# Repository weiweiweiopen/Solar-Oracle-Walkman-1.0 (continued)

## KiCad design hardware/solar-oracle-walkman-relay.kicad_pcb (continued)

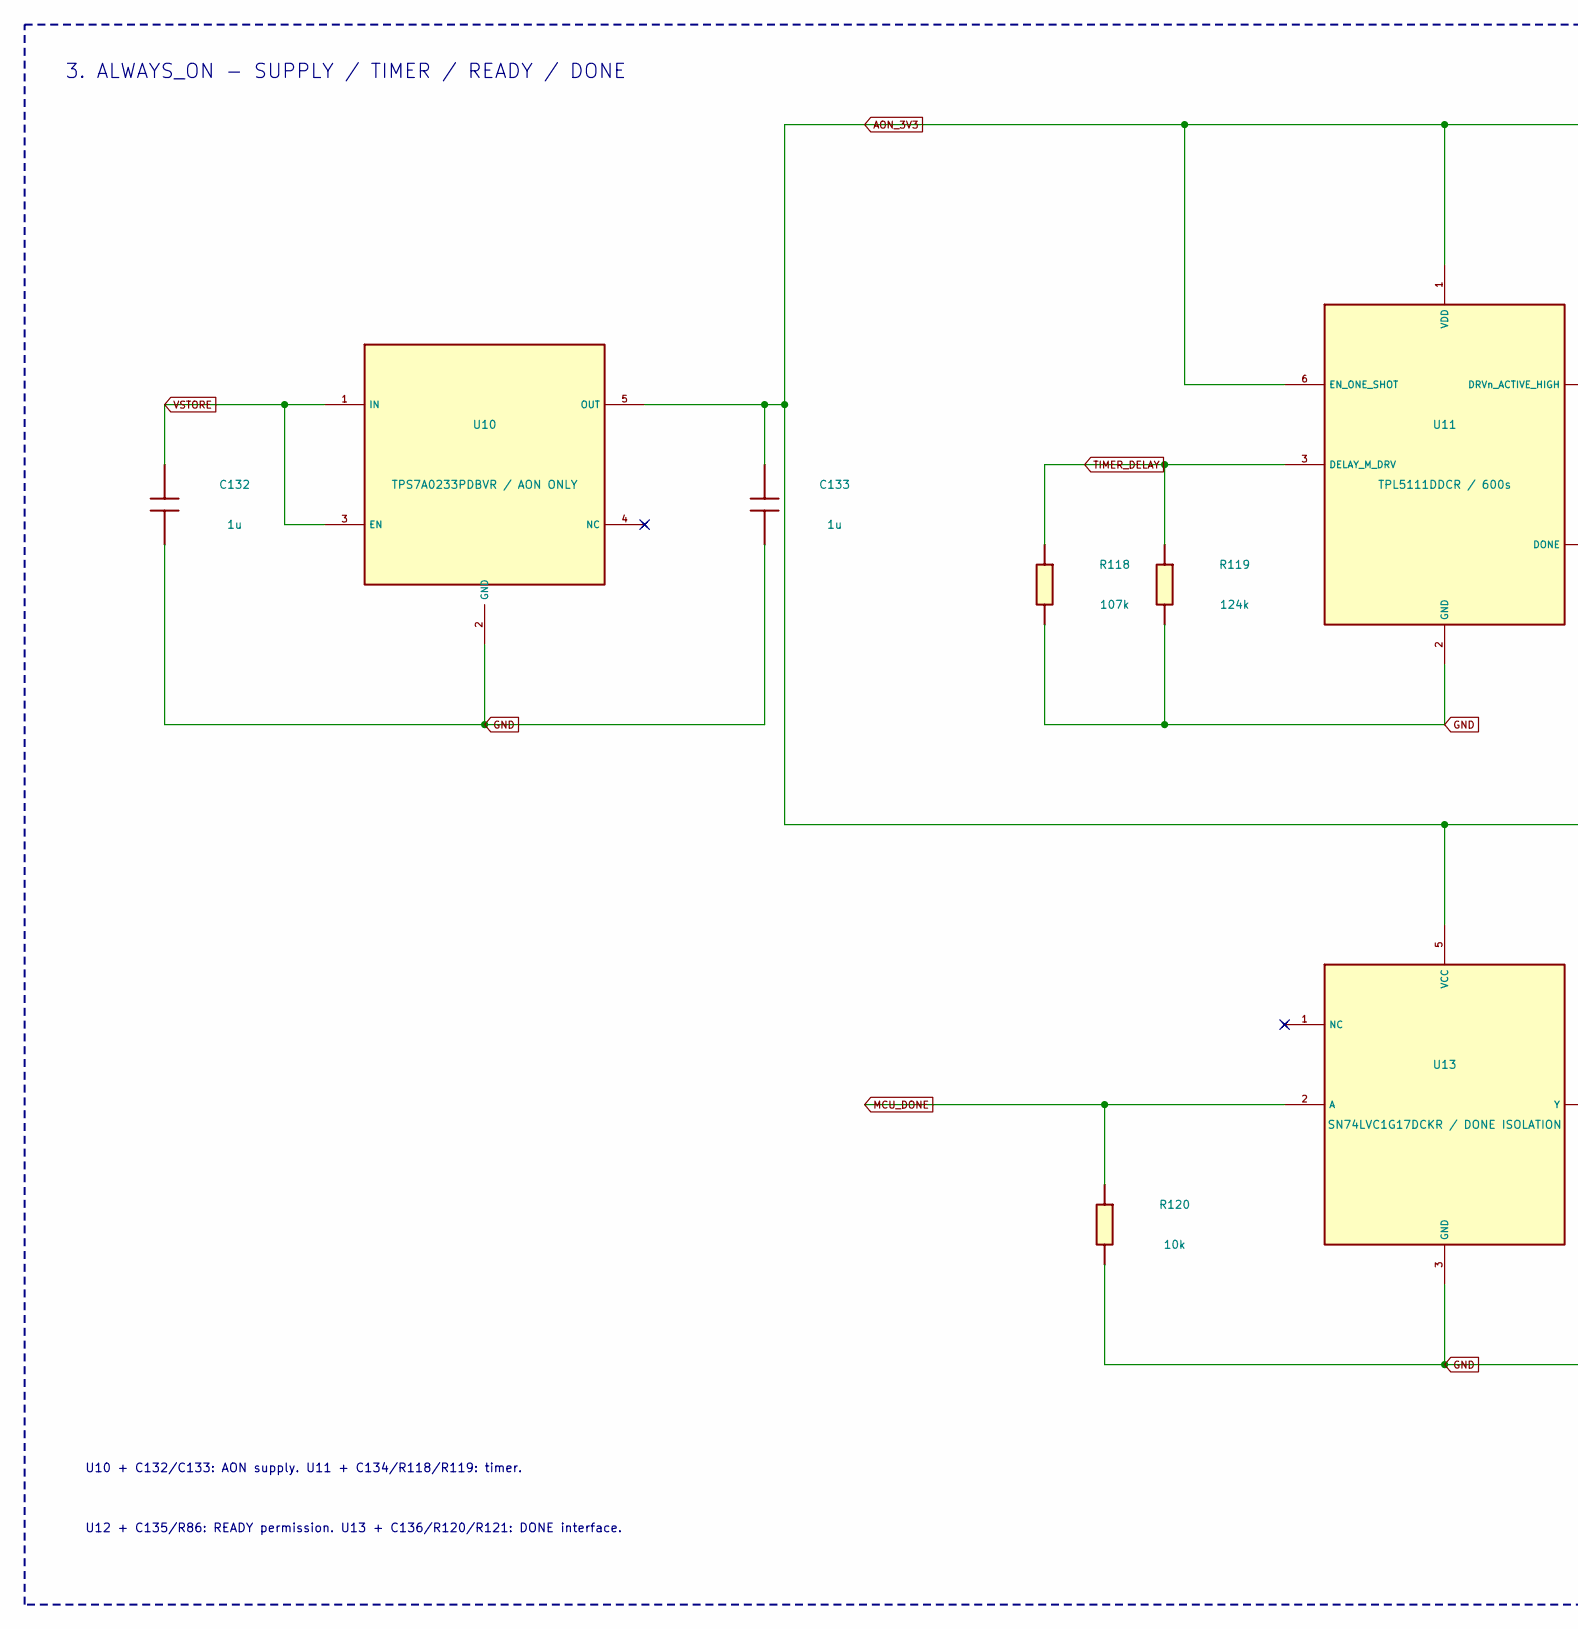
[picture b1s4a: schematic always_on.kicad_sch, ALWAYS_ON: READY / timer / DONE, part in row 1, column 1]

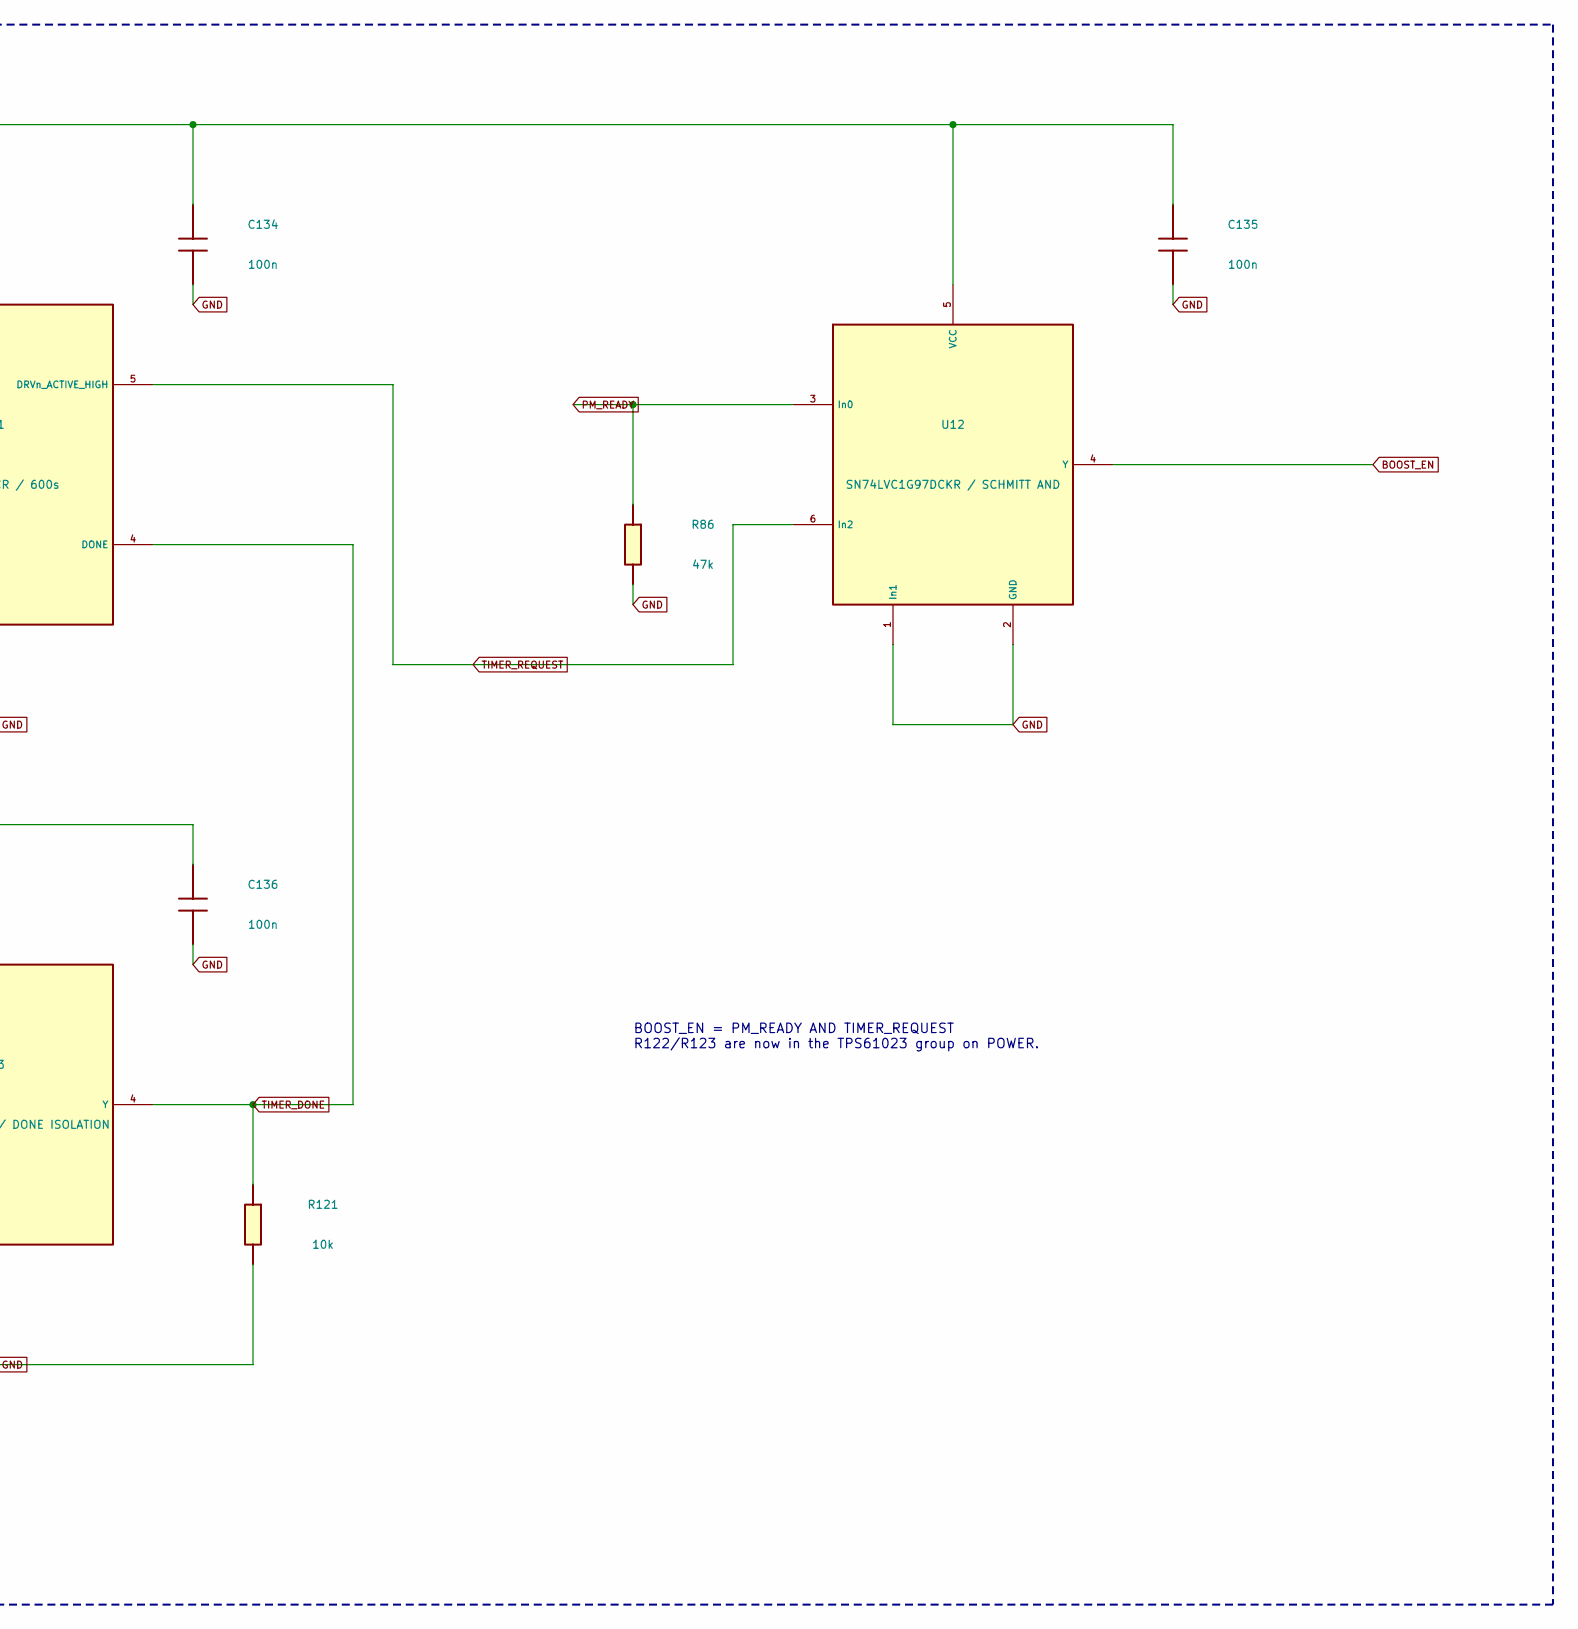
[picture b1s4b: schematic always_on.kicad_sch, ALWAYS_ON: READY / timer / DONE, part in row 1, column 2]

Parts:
C132, C133: 1u; C_0805_2012Metric; MPN GRM21BR71C105KA01L
C134, C135, C136: 100n; C_0805_2012Metric; MPN GRM21BR71H104KA01L
R86: 47k; R_0603_1608Metric; MPN RC0603FR-0747KL
R118: 107k; R_0603_1608Metric; MPN RC0603FR-07107KL
R119: 124k; R_0603_1608Metric; MPN RC0603FR-07124KL
R120, R121: 10k; R_0603_1608Metric; MPN RC0603FR-0710KL
U10: TPS7A0233PDBVR / AON ONLY; SOT-23-5; MPN TPS7A0233PDBVR
U11: TPL5111DDCR / 600s; SOT-23-6; MPN TPL5111DDCR
U12: SN74LVC1G97DCKR / SCHMITT AND; SOT-363_SC-70-6; MPN SN74LVC1G97DCKR
U13: SN74LVC1G17DCKR / DONE ISOLATION; SOT-353_SC-70-5; MPN SN74LVC1G17DCKR

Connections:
AON_3V3: C133.1, C134.1, C135.1, C136.1, U10.5 (OUT), U11.1 (VDD), U11.6 (EN_ONE_SHOT), U12.5 (VCC), U13.5 (VCC)
BOOST_EN: U12.4 (Y); also elsewhere on the board
GND: C132.2, C133.2, C134.2, C135.2, C136.2, R86.2, R118.2, R119.2, R120.2, R121.2, U10.2 (GND), U11.2 (GND), U12.1 (In1), U12.2 (GND), U13.3 (GND); also elsewhere on the board
MCU_DONE: R120.1, U13.2 (A); also elsewhere on the board
PM_READY: R86.1, U12.3 (In0); also elsewhere on the board
TIMER_DELAY: R118.1, R119.1, U11.3 (DELAY_M_DRV)
TIMER_DONE: R121.1, U11.4 (DONE), U13.4 (Y)
TIMER_REQUEST: U11.5 (DRVn_ACTIVE_HIGH), U12.6 (In2)
VSTORE: C132.1, U10.1 (IN), U10.3 (EN); also elsewhere on the board

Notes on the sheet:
U12 + C135/R86: READY permission. U13 + C136/R120/R121: DONE interface.
U10 + C132/C133: AON supply. U11 + C134/R118/R119: timer.
3. ALWAYS_ON - SUPPLY / TIMER / READY / DONE
BOOST_EN = PM_READY AND TIMER_REQUEST R122/R123 are now in the TPS61023 group on POWER.

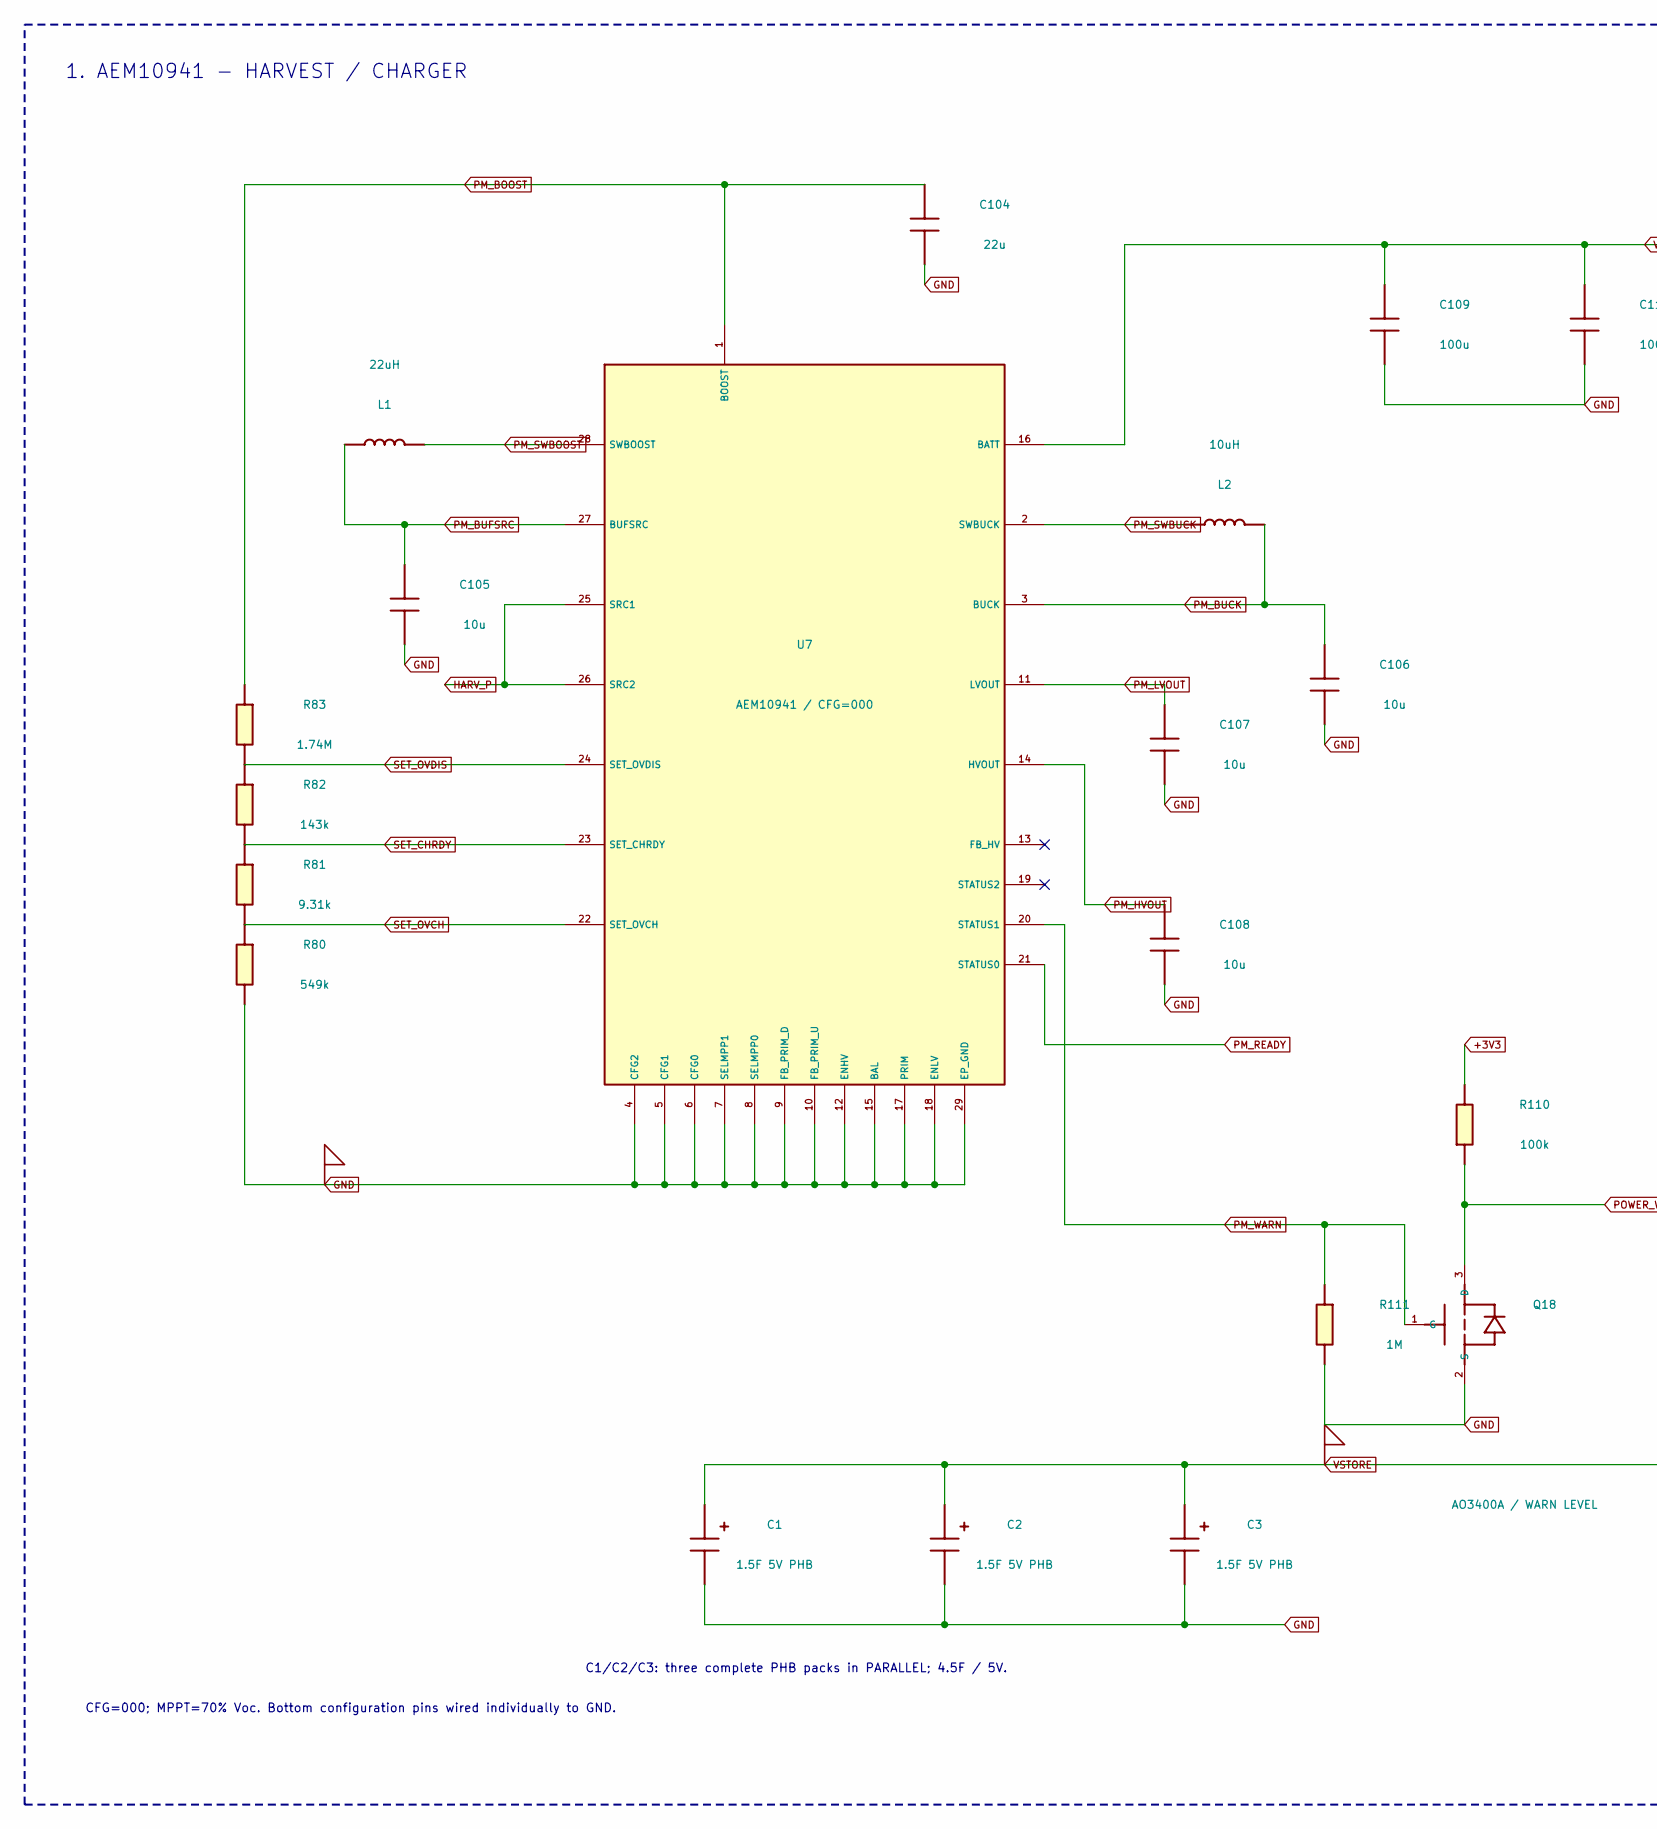
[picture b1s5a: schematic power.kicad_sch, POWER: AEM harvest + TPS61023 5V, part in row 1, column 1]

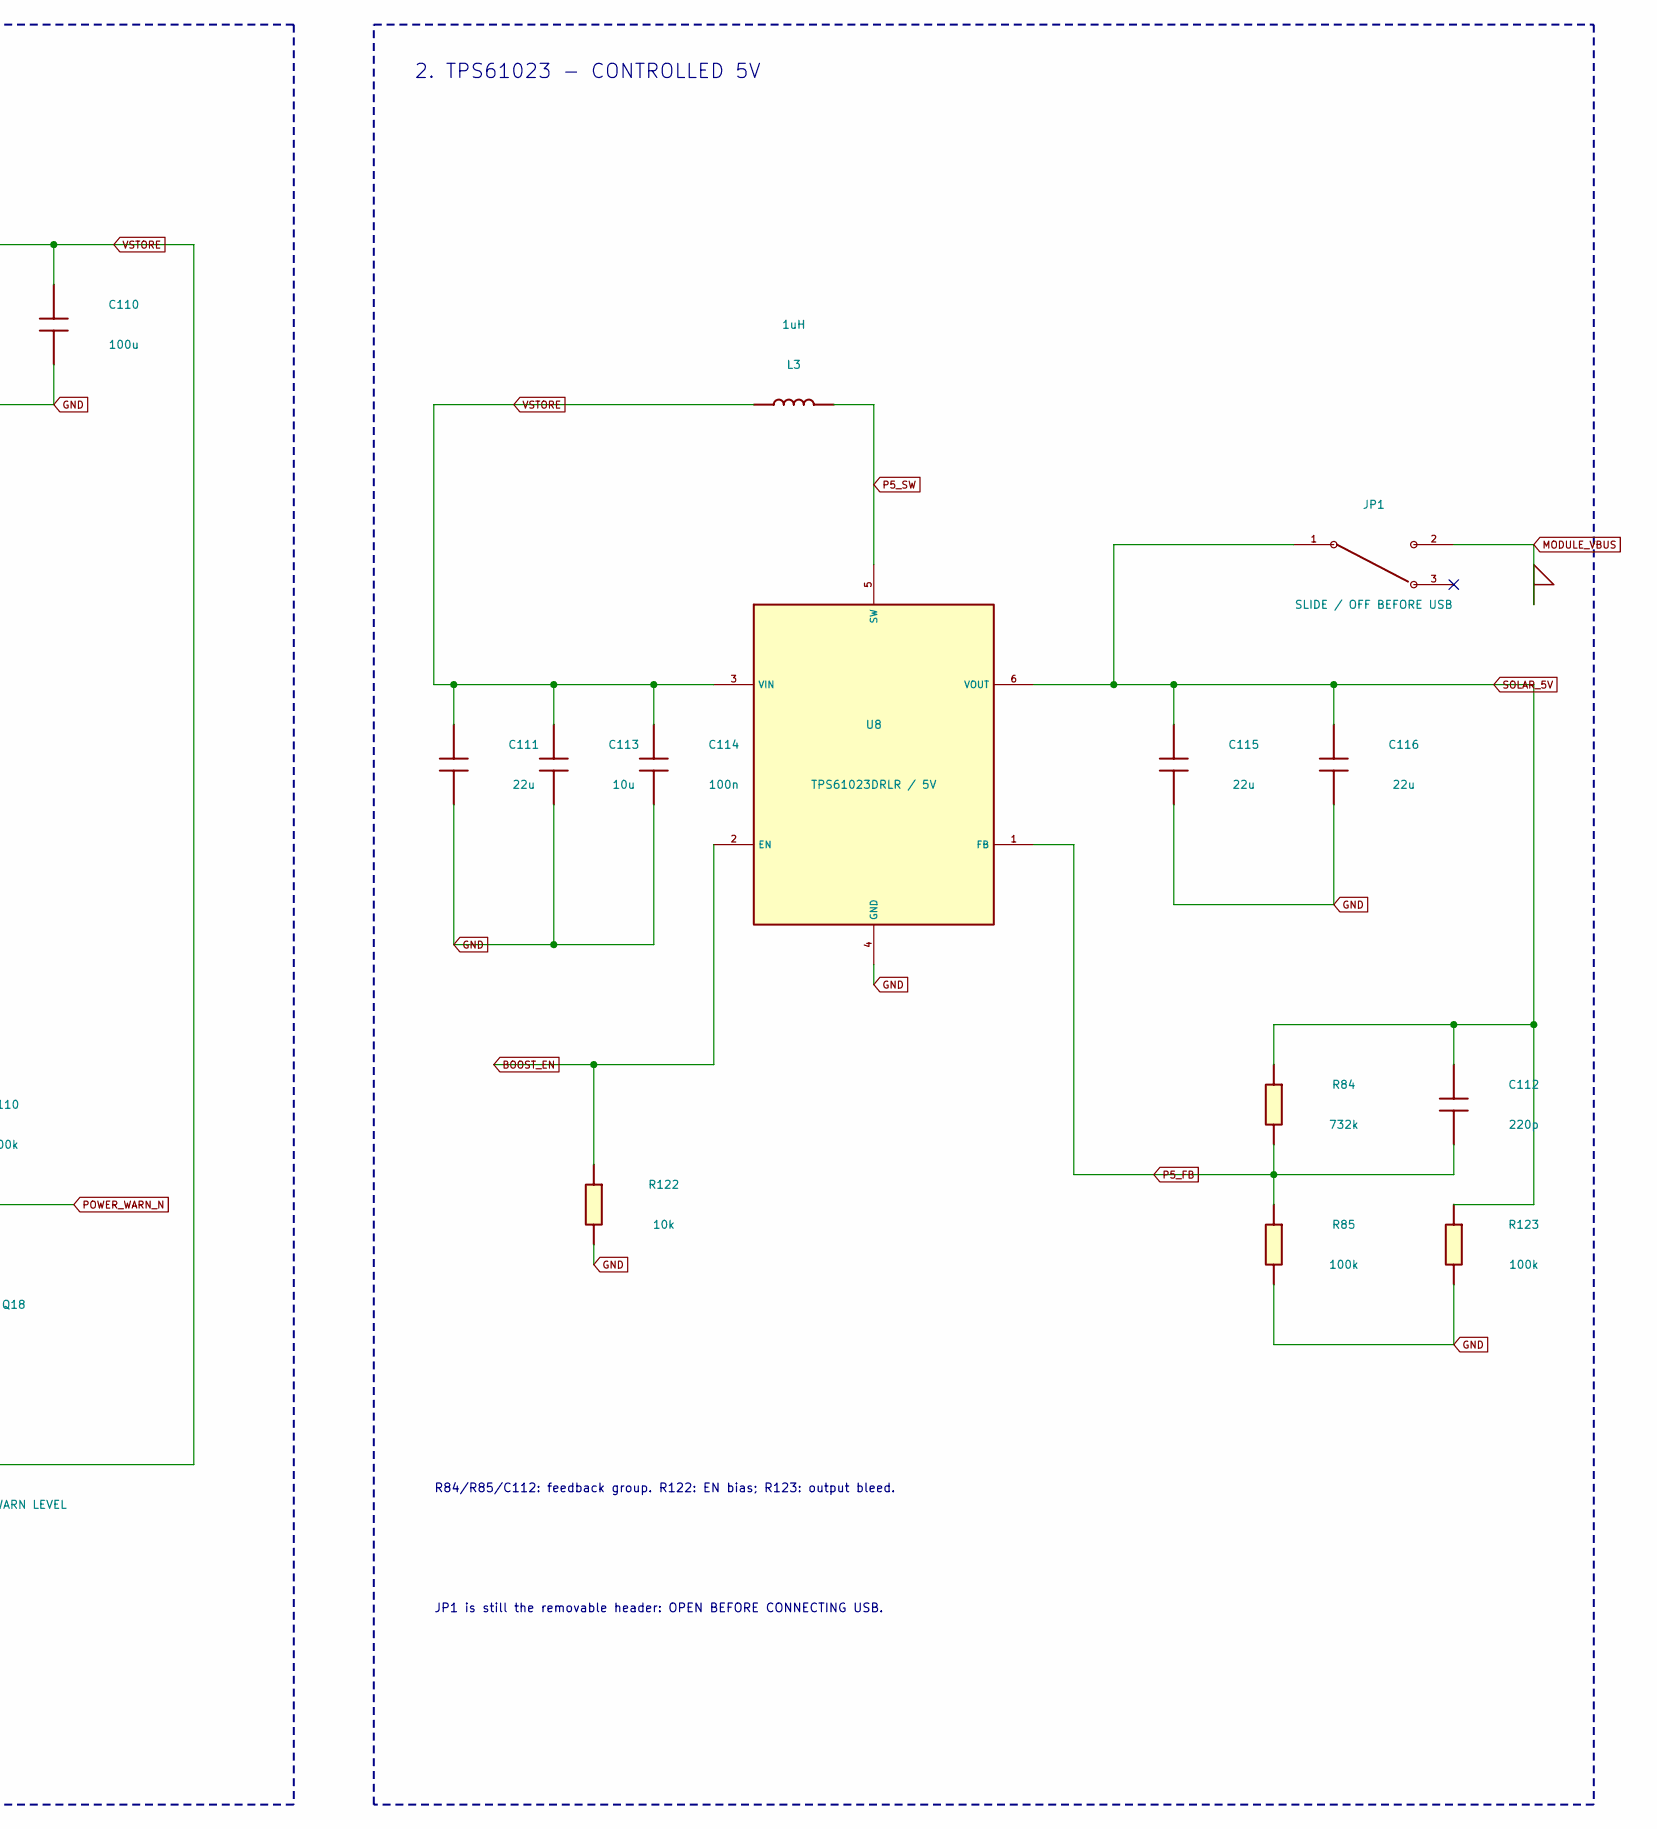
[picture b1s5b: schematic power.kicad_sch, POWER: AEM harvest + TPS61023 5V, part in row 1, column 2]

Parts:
C1, C2, C3: 1.5F 5V PHB; PHB_5R0V155_R_LaidDown_Provisional; MPN PHB-5R0V155-R
C104, C111, C115, C116: 22u; C_1210_3225Metric; MPN GRM32ER61A226KE20L
C105, C106, C107, C108, C113: 10u; C_0805_2012Metric; MPN GRM21BR61C106KE15L
C109, C110: 100u; C_1210_3225Metric; MPN GRM32ER60J107ME20L
C112: 220p; C_0603_1608Metric; MPN GRM1885C1H221JA01D
C114: 100n; C_0805_2012Metric; MPN GRM21BR71H104KA01L
JP1: SLIDE / OFF BEFORE USB; EGJ1210AAG2R_Side; MPN EGJ1210AAG2R
L1: 22uH; L_Coilcraft_LPS4018; MPN LPS4018-223MRC
L2: 10uH; L_TDK_MLZ1608; MPN MLZ1608N100LT000
L3: 1uH; Coilcraft_XEL4030; MPN XEL4030-102MEC
Q18: AO3400A / WARN LEVEL; SOT-23; MPN AO3400A
R80: 549k; R_1206_3216Metric; MPN TNPW1206549KBEEA
R81: 9.31k; R_1206_3216Metric; MPN TNPW12069K31BEEA
R82: 143k; R_1206_3216Metric; MPN TNPW1206143KBEEA
R83: 1.74M; R_1206_3216Metric; MPN TNPW12061M74BEEA
R84: 732k; R_0603_1608Metric; MPN RC0603FR-07732KL
R85, R110, R123: 100k; R_0603_1608Metric; MPN RC0603FR-07100KL
R111: 1M; R_0603_1608Metric; MPN RC0603FR-071ML
R122: 10k; R_0603_1608Metric; MPN RC0603FR-0710KL
U7: AEM10941 / CFG=000; AEM10941_QFN28_EP3.5; MPN 10AEM10941C0001
U8: TPS61023DRLR / 5V; SOT-563; MPN TPS61023DRLR

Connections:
+3V3: R110.2; also elsewhere on the board
BOOST_EN: R122.1, U8.2 (EN); also elsewhere on the board
GND: C1.2 (-), C2.2 (-), C3.2 (-), C104.2, C105.2, C106.2, C107.2, C108.2, C109.2, C110.2, C111.2, C113.2, C114.2, C115.2, C116.2, Q18.2 (S), R80.2, R85.2, R111.2, R122.2, R123.2, U7.4 (CFG2), U7.5 (CFG1), U7.6 (CFG0), U7.7 (SELMPP1), U7.8 (SELMPP0), U7.9 (FB_PRIM_D), U7.10 (FB_PRIM_U), U7.12 (ENHV), U7.15 (BAL), U7.17 (PRIM), U7.18 (ENLV), U7.29 (EP_GND), U8.4 (GND); also elsewhere on the board
HARV_P: U7.25 (SRC1), U7.26 (SRC2); also elsewhere on the board
MODULE_VBUS: JP1.2 (ON_MODULE_VBUS); also elsewhere on the board
P5_FB: C112.2, R84.2, R85.1, U8.1 (FB)
P5_SW: L3.2, U8.5 (SW)
PM_BOOST: C104.1, R83.1, U7.1 (BOOST)
PM_BUCK: C106.1, L2.2, U7.3 (BUCK)
PM_BUFSRC: C105.1, L1.1, U7.27 (BUFSRC)
PM_HVOUT: C108.1, U7.14 (HVOUT)
PM_LVOUT: C107.1, U7.11 (LVOUT)
PM_READY: U7.21 (STATUS0); also elsewhere on the board
PM_SWBOOST: L1.2, U7.28 (SWBOOST)
PM_SWBUCK: L2.1, U7.2 (SWBUCK)
PM_WARN: Q18.1 (G), R111.1, U7.20 (STATUS1)
POWER_WARN_N: Q18.3 (D), R110.1; also elsewhere on the board
SET_CHRDY: R81.1, R82.2, U7.23 (SET_CHRDY)
SET_OVCH: R80.1, R81.2, U7.22 (SET_OVCH)
SET_OVDIS: R82.1, R83.2, U7.24 (SET_OVDIS)
SOLAR_5V: C112.1, C115.1, C116.1, JP1.1 (COM_SOLAR_5V), R84.1, R123.1, U8.6 (VOUT)
VSTORE: C1.1 (+), C2.1 (+), C3.1 (+), C109.1, C110.1, C111.1, C113.1, C114.1, L3.1, U7.16 (BATT), U8.3 (VIN); also elsewhere on the board

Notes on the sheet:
JP1 is still the removable header: OPEN BEFORE CONNECTING USB.
2. TPS61023 - CONTROLLED 5V
1. AEM10941 - HARVEST / CHARGER
CFG=000; MPPT=70% Voc. Bottom configuration pins wired individually to GND.
R84/R85/C112: feedback group. R122: EN bias; R123: output bleed.
C1/C2/C3: three complete PHB packs in PARALLEL; 4.5F / 5V.

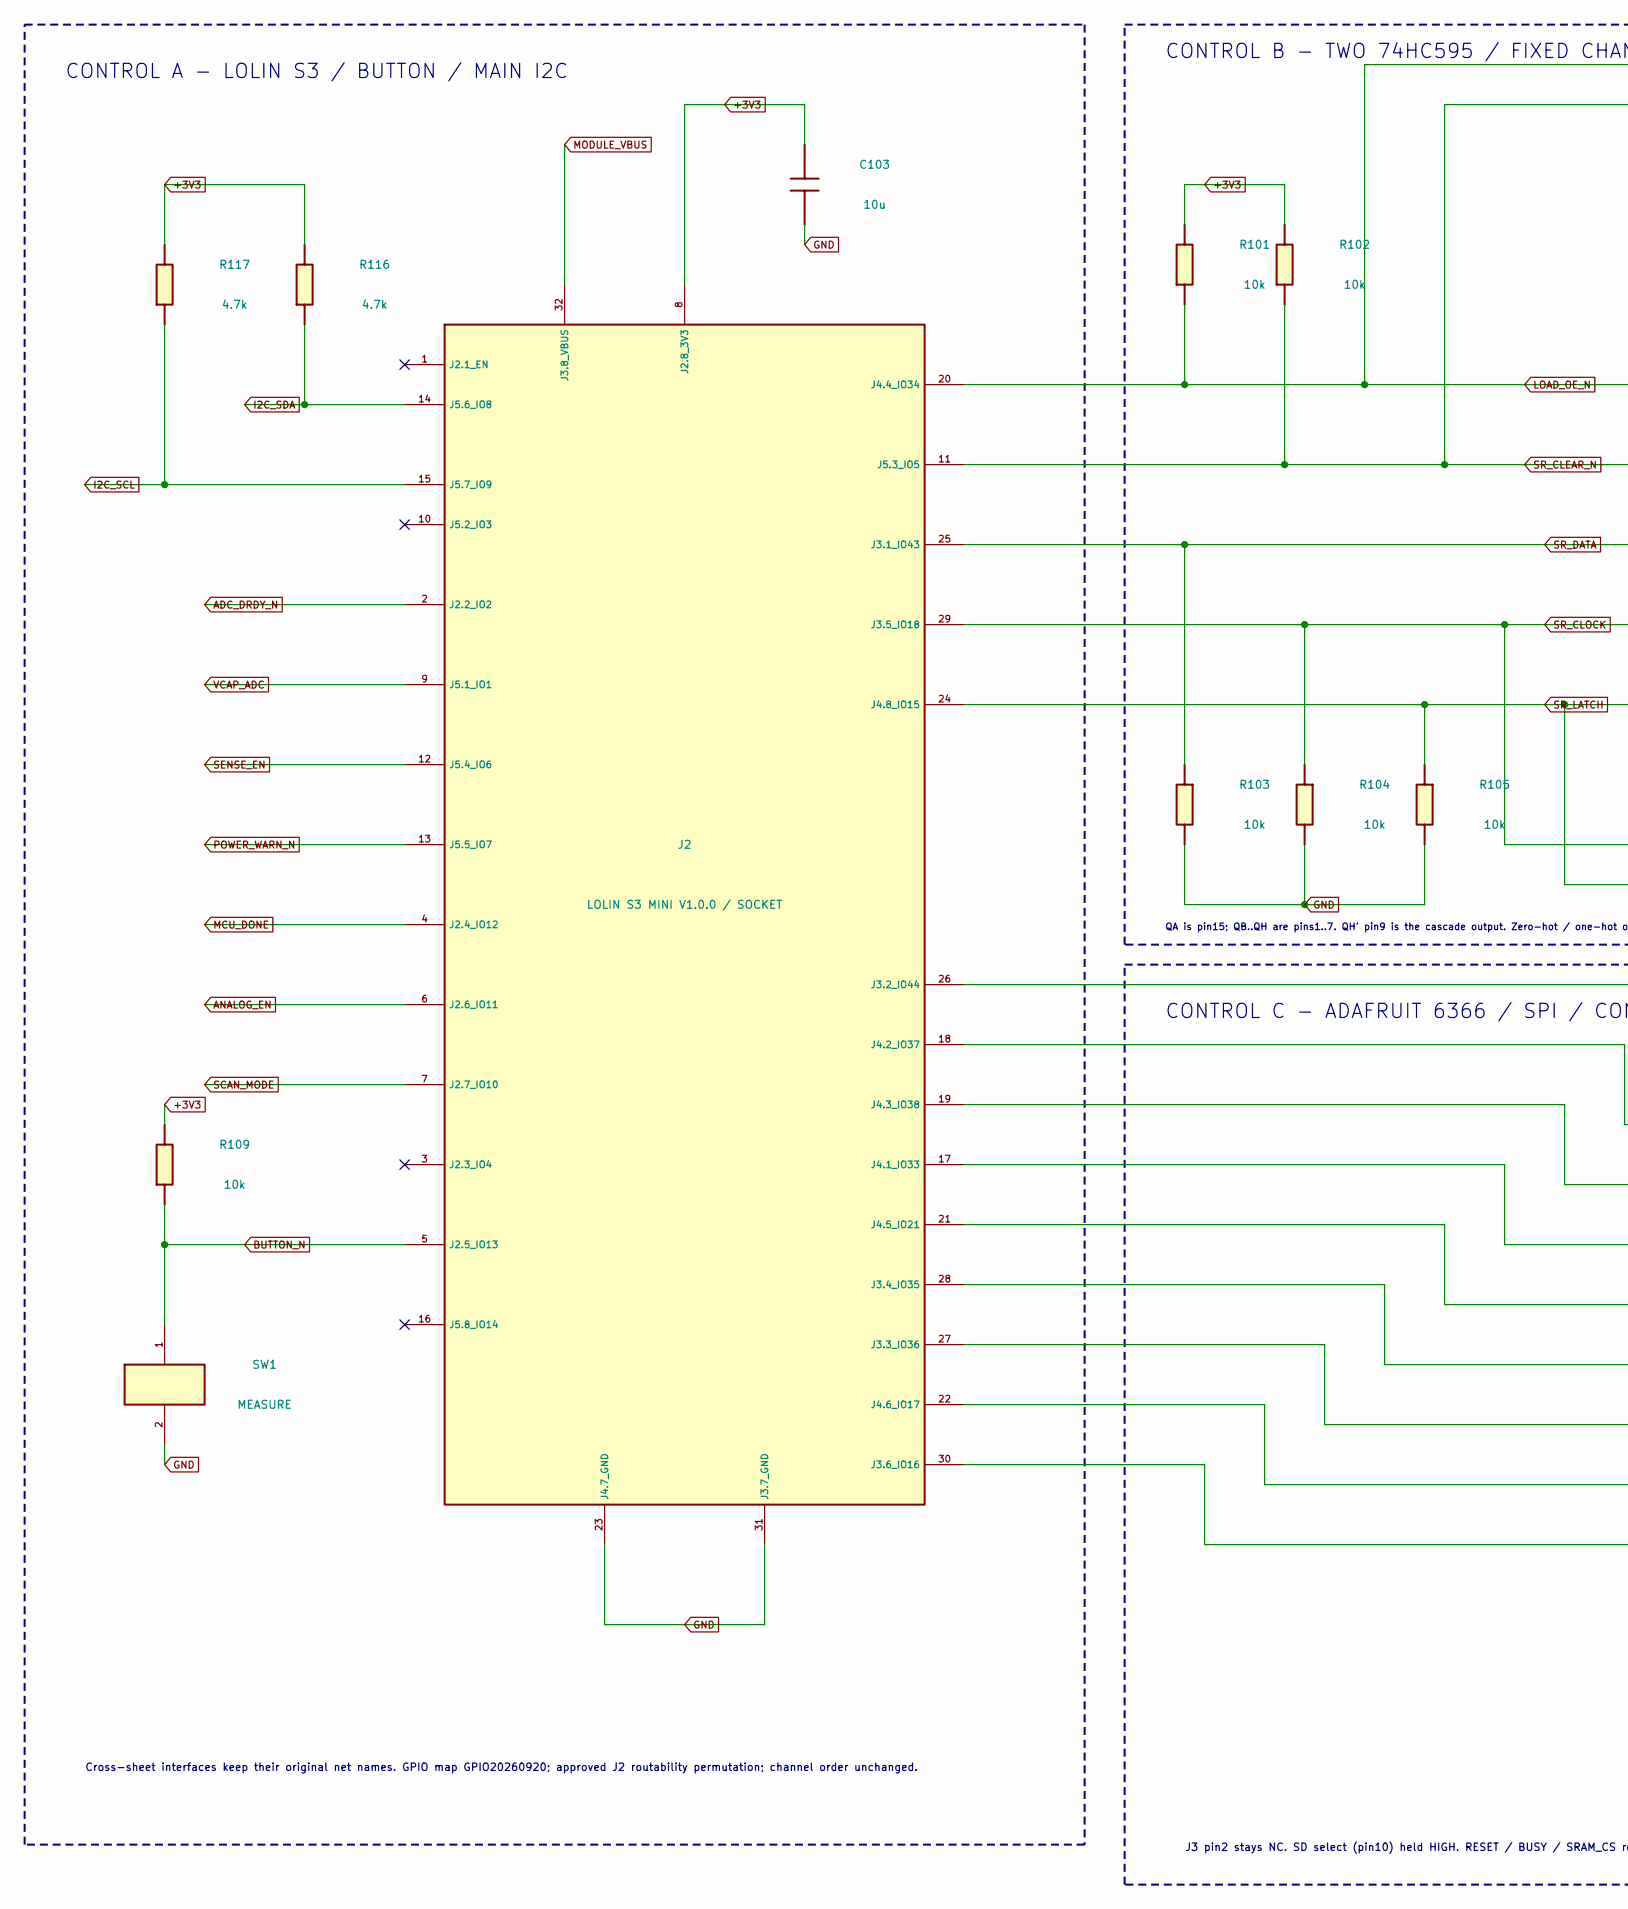
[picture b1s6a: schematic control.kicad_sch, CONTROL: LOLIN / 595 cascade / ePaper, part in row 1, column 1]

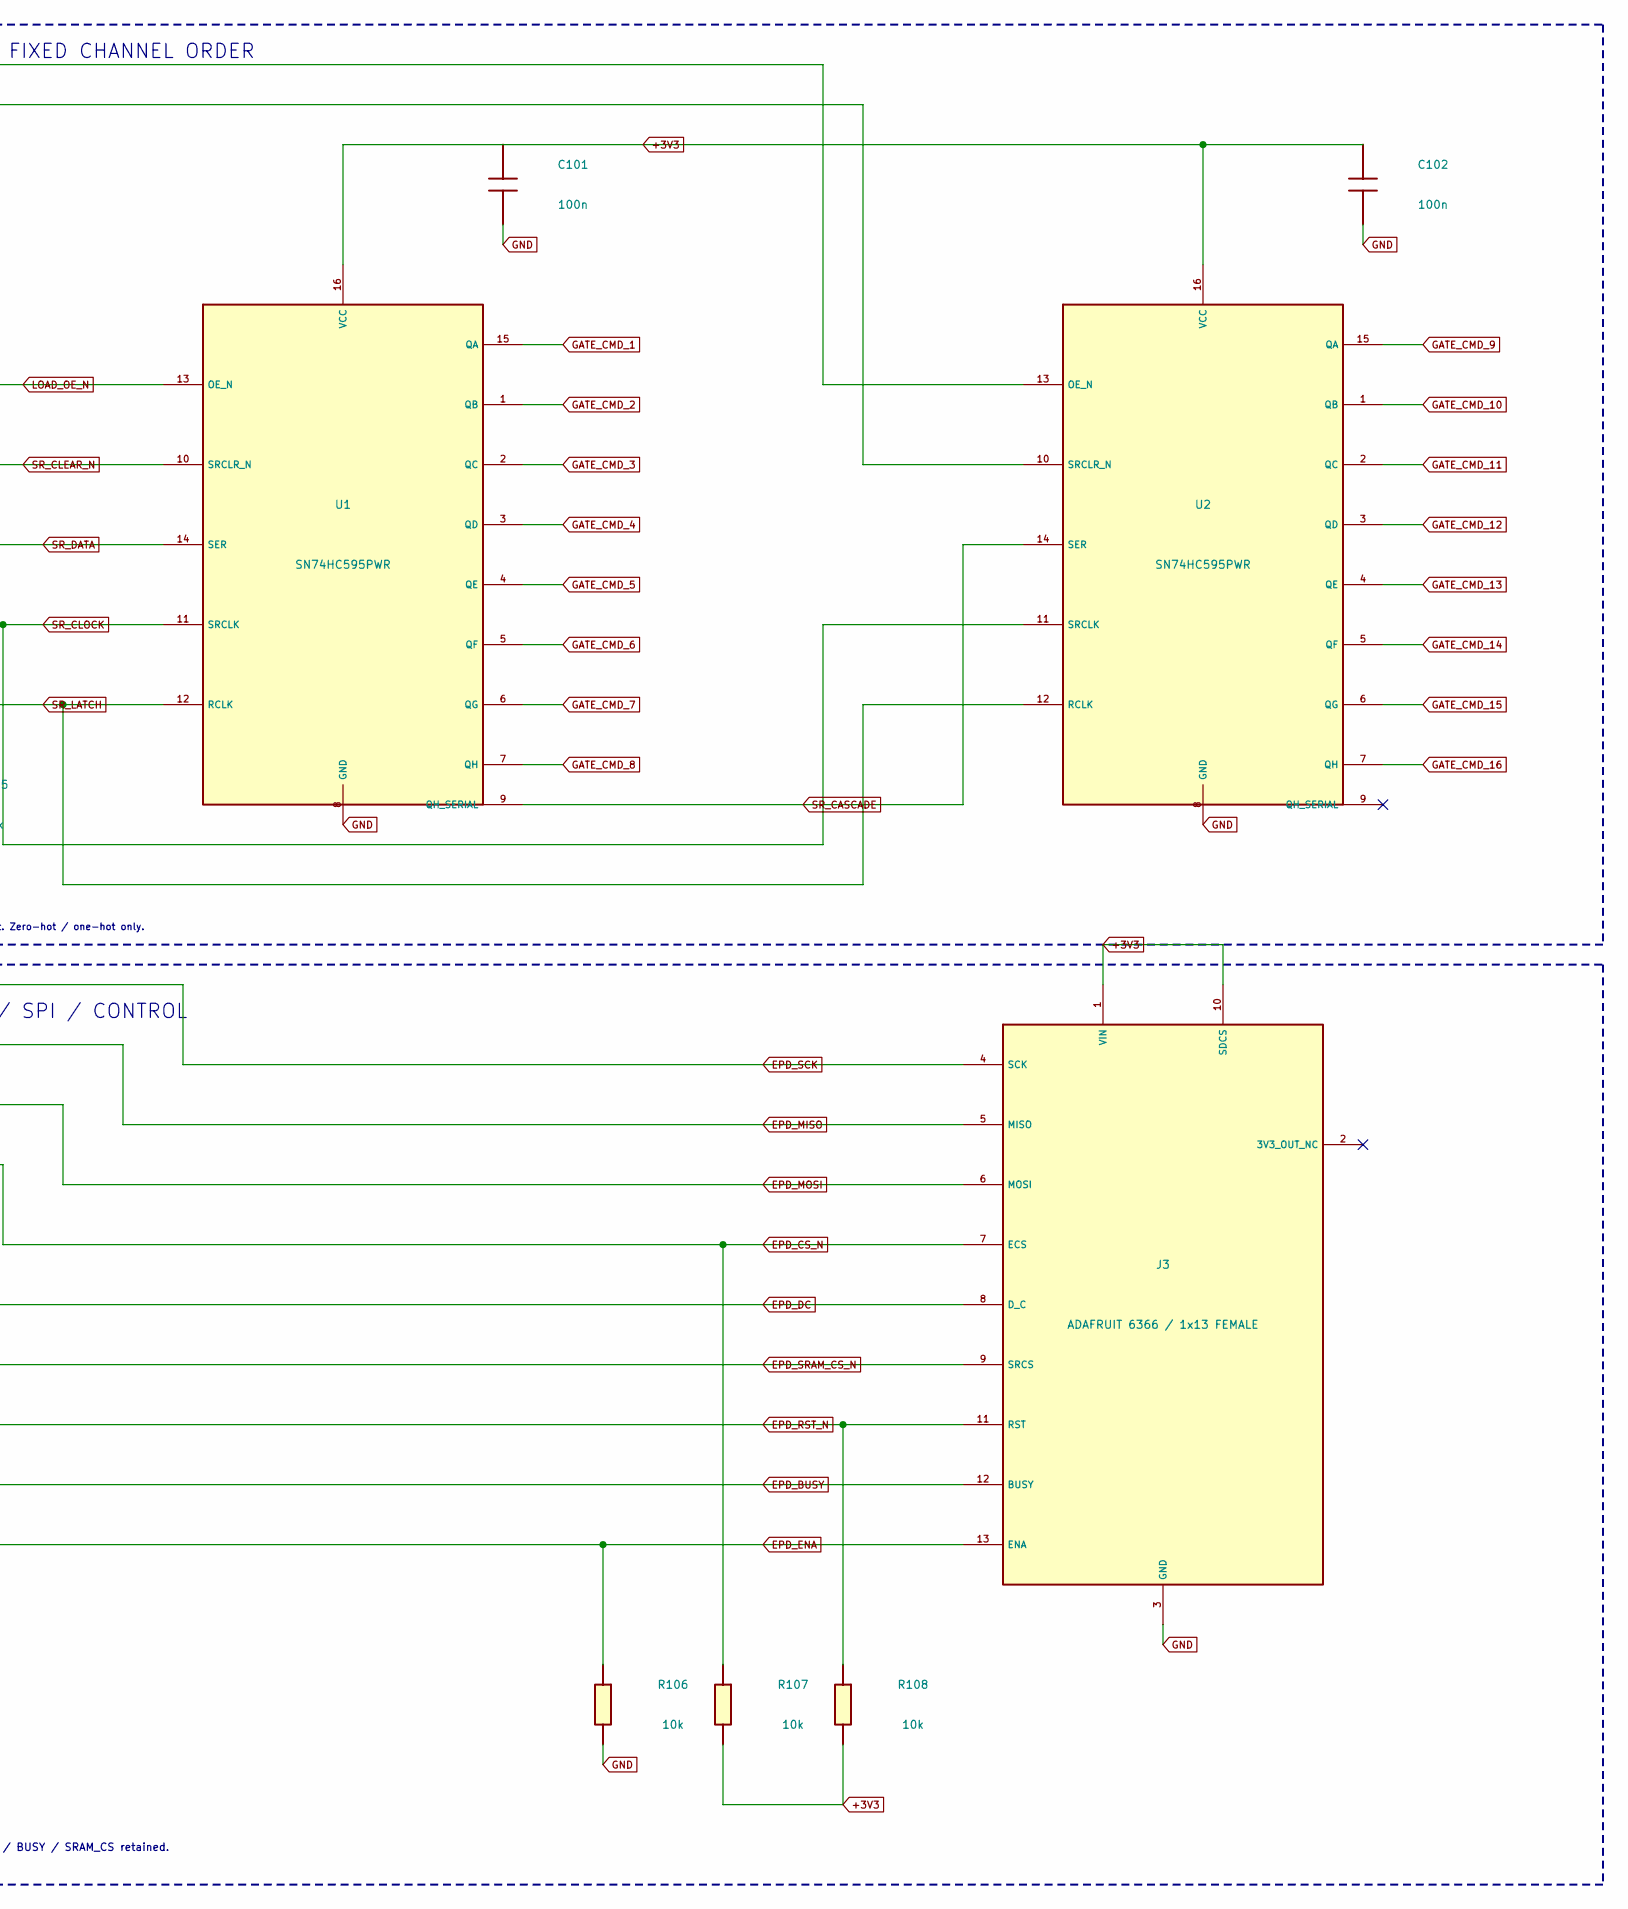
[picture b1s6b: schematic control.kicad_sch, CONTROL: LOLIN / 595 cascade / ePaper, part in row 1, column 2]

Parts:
C101, C102: 100n; C_0805_2012Metric; MPN GRM21BR71H104KA01L
C103: 10u; C_0805_2012Metric; MPN GRM21BR61C106KE15L
J2: LOLIN S3 MINI V1.0.0 / SOCKET; LOLIN_S3_Mini_V1; MPN LOLIN S3 MINI V1.0.0
J3: ADAFRUIT 6366 / 1x13 FEMALE; EPD_6366_Socket13; MPN SSW-113-01-T-S
R101, R102, R103, R104, R105, R106, R107, R108, R109: 10k; R_0603_1608Metric; MPN RC0603FR-0710KL
R116, R117: 4.7k; R_0603_1608Metric; MPN RC0603FR-074K7L
SW1: MEASURE; SW_SPST_TL3342; MPN TL3342F160QG
U1, U2: SN74HC595PWR; TSSOP-16_4.4x5mm_P0.65mm; MPN SN74HC595PWR

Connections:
+3V3: C101.1, C102.1, C103.1, J2.8 (J2.8_3V3), J3.1 (VIN), J3.10 (SDCS), R101.2, R102.2, R107.2, R108.2, R109.2, R116.2, R117.2, U1.16 (VCC), U2.16 (VCC); also elsewhere on the board
ADC_DRDY_N: J2.2 (J2.2_IO2); also elsewhere on the board
ANALOG_EN: J2.6 (J2.6_IO11); also elsewhere on the board
BUTTON_N: J2.5 (J2.5_IO13), R109.1, SW1.1 (BUTTON)
EPD_BUSY: J2.22 (J4.6_IO17), J3.12 (BUSY)
EPD_CS_N: J2.17 (J4.1_IO33), J3.7 (ECS), R107.1
EPD_DC: J2.21 (J4.5_IO21), J3.8 (D_C)
EPD_ENA: J2.30 (J3.6_IO16), J3.13 (ENA), R106.1
EPD_MISO: J2.18 (J4.2_IO37), J3.5 (MISO)
EPD_MOSI: J2.19 (J4.3_IO38), J3.6 (MOSI)
EPD_RST_N: J2.27 (J3.3_IO36), J3.11 (RST), R108.1
EPD_SCK: J2.26 (J3.2_IO44), J3.4 (SCK)
EPD_SRAM_CS_N: J2.28 (J3.4_IO35), J3.9 (SRCS)
GATE_CMD_1: U1.15 (QA); also elsewhere on the board
GATE_CMD_2: U1.1 (QB); also elsewhere on the board
GATE_CMD_3: U1.2 (QC); also elsewhere on the board
GATE_CMD_4: U1.3 (QD); also elsewhere on the board
GATE_CMD_5: U1.4 (QE); also elsewhere on the board
GATE_CMD_6: U1.5 (QF); also elsewhere on the board
GATE_CMD_7: U1.6 (QG); also elsewhere on the board
GATE_CMD_8: U1.7 (QH); also elsewhere on the board
GATE_CMD_9: U2.15 (QA); also elsewhere on the board
GATE_CMD_10: U2.1 (QB); also elsewhere on the board
GATE_CMD_11: U2.2 (QC); also elsewhere on the board
GATE_CMD_12: U2.3 (QD); also elsewhere on the board
GATE_CMD_13: U2.4 (QE); also elsewhere on the board
GATE_CMD_14: U2.5 (QF); also elsewhere on the board
GATE_CMD_15: U2.6 (QG); also elsewhere on the board
GATE_CMD_16: U2.7 (QH); also elsewhere on the board
GND: C101.2, C102.2, C103.2, J2.23 (J4.7_GND), J2.31 (J3.7_GND), J3.3 (GND), R103.2, R104.2, R105.2, R106.2, SW1.2 (GND), U1.8 (GND), U2.8 (GND); also elsewhere on the board
I2C_SCL: J2.15 (J5.7_IO9), R117.1; also elsewhere on the board
I2C_SDA: J2.14 (J5.6_IO8), R116.1; also elsewhere on the board
LOAD_OE_N: J2.20 (J4.4_IO34), R101.1, U1.13 (OE_N), U2.13 (OE_N)
MCU_DONE: J2.4 (J2.4_IO12); also elsewhere on the board
MODULE_VBUS: J2.32 (J3.8_VBUS); also elsewhere on the board
POWER_WARN_N: J2.13 (J5.5_IO7); also elsewhere on the board
SCAN_MODE: J2.7 (J2.7_IO10); also elsewhere on the board
SENSE_EN: J2.12 (J5.4_IO6); also elsewhere on the board
SR_CASCADE: U1.9 (QH_SERIAL), U2.14 (SER)
SR_CLEAR_N: J2.11 (J5.3_IO5), R102.1, U1.10 (SRCLR_N), U2.10 (SRCLR_N)
SR_CLOCK: J2.29 (J3.5_IO18), R104.1, U1.11 (SRCLK), U2.11 (SRCLK)
SR_DATA: J2.25 (J3.1_IO43), R103.1, U1.14 (SER)
SR_LATCH: J2.24 (J4.8_IO15), R105.1, U1.12 (RCLK), U2.12 (RCLK)
VCAP_ADC: J2.9 (J5.1_IO1); also elsewhere on the board

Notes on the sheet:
J3 pin2 stays NC. SD select (pin10) held HIGH. RESET / BUSY / SRAM_CS retained.
Cross-sheet interfaces keep their original net names. GPIO map GPIO20260920; approved J2 routability permutation; channel order unchanged.
QA is pin15; QB..QH are pins1..7. QH' pin9 is the cascade output. Zero-hot / one-hot only.
CONTROL B - TWO 74HC595 / FIXED CHANNEL ORDER
CONTROL C - ADAFRUIT 6366 / SPI / CONTROL
CONTROL A - LOLIN S3 / BUTTON / MAIN I2C
